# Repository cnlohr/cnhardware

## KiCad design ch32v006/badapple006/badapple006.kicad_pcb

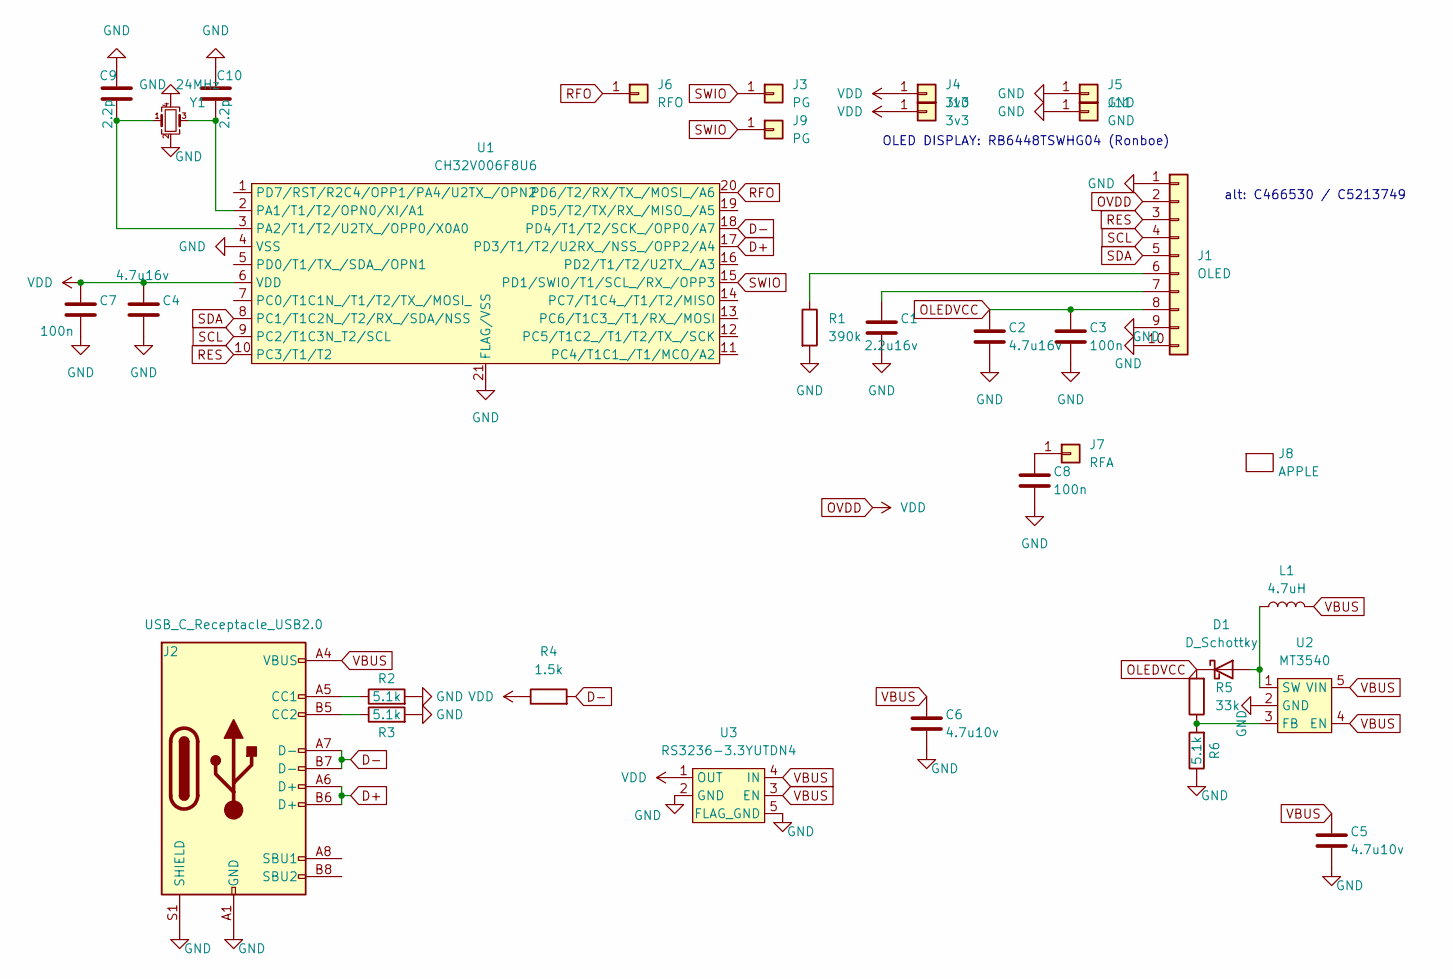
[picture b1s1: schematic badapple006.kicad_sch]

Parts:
C1: 2.2u16v; C_0402_1005Metric; LCSC C72203
C2: 4.7u16v; C_0603_1608Metric; LCSC C77045
C3, C7, C8: 100n; C_0402_1005Metric; LCSC C1525
C4: 4.7u16v; C_0402_1005Metric; LCSC C72203
C5, C6: 4.7u10v; C_0402_1005Metric; LCSC C23733
C9, C10: 2.2p; C_0402_1005Metric; LCSC C1559
D1: D_Schottky; D_SOD-323; LCSC C191023
J1: OLED; AFC42-S08FMA-1H; LCSC C466530
J2: USB_C_Receptacle_USB2.0; USB_C_Receptacle_HRO_TYPE-C-31-M-12; LCSC C2765186
J3, J9: PG; TestPoint_Pad_D1.0mm
J4, J10: 3v3; TestPoint_Pad_D1.0mm
J5, J11: GND; TestPoint_Pad_D1.0mm
J6: RFO; TestPoint_Pad_D1.0mm
J7: RFA; TestPoint_Pad_D1.0mm
J8: APPLE; apple
L1: 4.7uH; L_0603_1608Metric; LCSC C114862
R1: 390k; R_0402_1005Metric; LCSC C25782
R2, R3, R6: 5.1k; R_0402_1005Metric; LCSC C105872
R4: 1.5k; R_0402_1005Metric; LCSC C25867
R5: 33k; R_0402_1005Metric; LCSC C25779
U1: CH32V006F8U6; QFN-20-1EP_3x3mm_P0.4mm_EP1.65x1.65mm
U2: MT3540; SOT-23-5; LCSC C181744
U3: RS3236-3.3YUTDN4; xdfn-reg; LCSC C379350
Y1: 24MHz; Crystal_SMD_2016-4Pin_2.0x1.6mm; LCSC C2929397

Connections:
D+: J2.A6 (D+), J2.B6 (D+), U1.17 (PD3/T1/T2/U2RX_/NSS_/OPP2/A4)
D-: J2.A7 (D-), J2.B7 (D-), R4.2, U1.18 (PD4/T1/T2/SCK_/OPP0/A7)
GND: C1.2, C2.2, C3.2, C4.2, C5.2, C6.2, C7.2, C8.2, C9.1, C10.1, J1.1, J1.9, J1.10, J2.A1 (GND), J2.A12 (GND), J2.B1 (GND), J2.B12 (GND), J2.S1 (SHIELD), J5.1, J11.1, R1.2, R2.2, R3.2, R6.1, U1.4 (VSS), U1.21 (FLAG/VSS), U2.2 (GND), U3.2 (GND), U3.5 (FLAG_GND), Y1.2, Y1.4
unnamed: D1.2 (A), L1.1, U2.1 (SW)
unnamed: J1.6, R1.1
unnamed: C1.1, J1.7
unnamed: J2.A5 (CC1), R2.1
unnamed: J2.B5 (CC2), R3.1
unnamed: C8.1, J7.1
unnamed: C10.2, U1.2 (PA1/T1/T2/OPN0/XI/A1), Y1.3
unnamed: C9.2, U1.3 (PA2/T1/T2/U2TX_/OPP0/X0A0), Y1.1
unnamed: R5.1, R6.2, U2.3 (FB)
OLEDVCC: C2.1, C3.1, D1.1 (K), J1.8, R5.2
OVDD: C4.1, C7.1, J1.2, J4.1, J10.1, R4.1, U1.6 (VDD), U3.1 (OUT)
RES: J1.3, U1.10 (PC3/T1/T2)
RFO: J6.1, U1.20 (PD6/T2/RX/TX_/MOSI_/A6)
SCL: J1.4, U1.9 (PC2/T1C3N_T2/SCL)
SDA: J1.5, U1.8 (PC1/T1C2N_/T2/RX_/SDA/NSS)
SWIO: J3.1, J9.1, U1.15 (PD1/SWIO/T1/SCL_/RX_/OPP3)
VBUS: C5.1, C6.1, J2.A4 (VBUS), J2.A9 (VBUS), J2.B4 (VBUS), J2.B9 (VBUS), L1.2, U2.4 (EN), U2.5 (VIN), U3.3 (EN), U3.4 (IN)

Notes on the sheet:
alt: C466530 / C5213749
OLED DISPLAY: RB6448TSWHG04 (Ronboe)

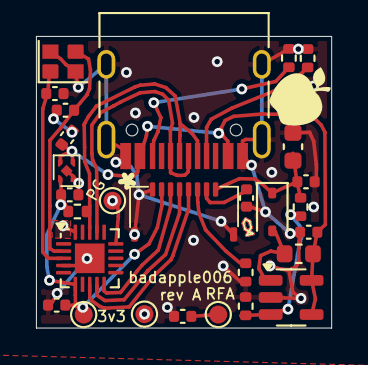
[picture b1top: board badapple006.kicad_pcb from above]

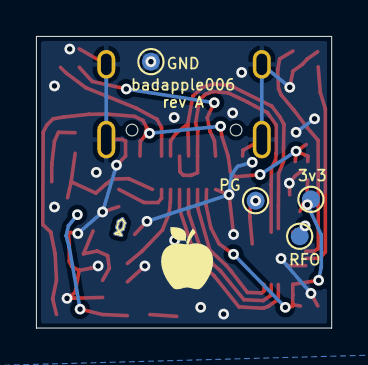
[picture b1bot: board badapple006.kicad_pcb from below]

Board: 2 copper layers, 16.4 x 16.2 mm, 34 parts (5 on the bottom side), 20 nets.

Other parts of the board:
J8#2: APPLE; apple

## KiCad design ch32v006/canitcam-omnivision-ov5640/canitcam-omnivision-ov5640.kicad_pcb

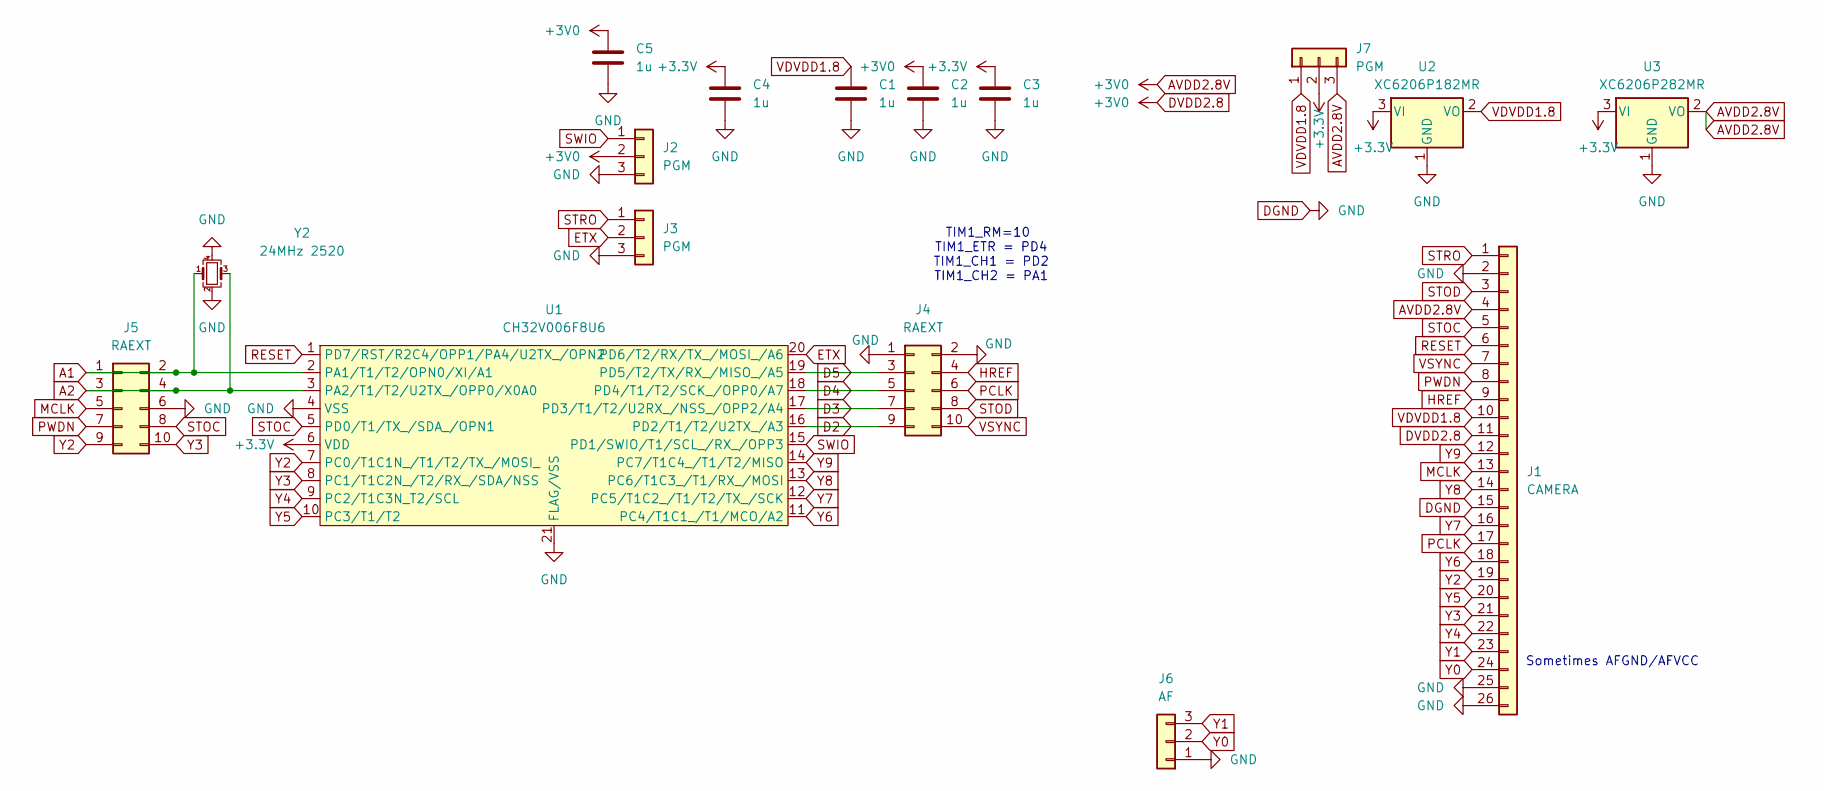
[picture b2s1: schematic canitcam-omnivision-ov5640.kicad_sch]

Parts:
C1, C2, C3, C4, C5: 1u; C_0402_1005Metric; LCSC C52923
J1: CAMERA; XUNPU_FPC-05F-24PH15; LCSC C2856831
J2, J3, J7: PGM; PinHeader_1x03_P2.54mm_Vertical; LCSC C2937625
J4, J5: RAEXT; PinHeader_2x05_P2.54mm_Vertical; LCSC C492422
J6: AF; PinHeader_1x03_P2.54mm_Vertical; LCSC C2937625
U1: CH32V006F8U6; QFN-20-1EP_3x3mm_P0.4mm_EP1.65x1.65mm; LCSC C42431288
U2: XC6206P182MR; SOT-23; LCSC C347373
U3: XC6206P282MR; SOT-23; LCSC C347374
Y2: 24MHz 2520; Crystal_SMD_2520-4Pin_2.5x2.0mm; LCSC C2965580

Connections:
+3.3V: C3.1, C4.1, J7.2, U1.6 (VDD), U2.3 (VI), U3.3 (VI)
A1: J5.1, J5.2, U1.2 (PA1/OSCI/A1/T1CH2/OPN0), Y2.1
A2: J5.3, J5.4, U1.3 (PA2/OSCO/A0/T1CH2N/OPP0/AETR2), Y2.3
AVDD2.8V: C2.1, C5.1, J1.4, J1.11, J2.2, J7.3, U3.2 (VO)
D2: J4.9, U1.16 (PD2/A3/T1CH1/T2CH3/T1CH2N)
D3: J4.7, U1.17 (PD3/A4/T2CH2/AETR/UCTS/T1CH4)
D4: J4.5, U1.18 (PD4/A7/UCK/T2CH1ETR/OPO/T1CH4ETR)
D5: J4.3, U1.19 (PD5/A5/UTX/T2CH4/URX)
DGND: C1.2, C2.2, C3.2, C4.2, C5.2, J1.2, J1.15, J1.25, J1.26, J2.3, J3.3, J4.1, J4.2, J5.6, J6.1, U1.4 (VSS), U1.21 (GND), U2.1 (GND), U3.1 (GND), Y2.2, Y2.4
ETX: J3.2, U1.20 (PD6/A7/URX/T2CH3/UTX)
HREF: J1.9, J4.4
MCLK: J1.13, J5.5
PCLK: J1.17, J4.6
PWDN: J1.8, J5.7
RESET: J1.6, U1.1 (PD7/NRST/T2CH4/OPP1/UCK)
STOC: J1.5, J5.8, U1.5 (PD0/T1CH1N/OPN1/SDA/UTX)
STOD: J1.3, J4.8
STRO: J1.1, J3.1
SWIO: J2.1, U1.15 (PD1/SWIO/AETR/T1CH3/SCL/URX)
VDVDD1.8: C1.1, J1.10, J7.1, U2.2 (VO)
VSYNC: J1.7, J4.10
Y0: J1.24, J6.2
Y1: J1.23, J6.3
Y2: J1.19, J5.9, U1.7 (PC0/T2CH3/UTX/NSS/T1CH3)
Y3: J1.21, J5.10, U1.8 (PC1/SDA/NSS/T2CH4/T2CH1ETR/T1BKIN/URX)
Y4: J1.22, U1.9 (PC2/SCL/URTS/T1BKIN/AETR/T2CH2/T1ETR)
Y5: J1.20, U1.10 (PC3/T1CH3/T1CHIN/UCTS)
Y6: J1.18, U1.11 (PC4/A2/T1CH4/MCO/T1CH1CH2N)
Y7: J1.16, U1.12 (PC5/SCK/T1ETR/T2CH1ETR/SCL/UCK/T1CH3)
Y8: J1.14, U1.13 (PC6/MOSI/T1CH1CH3/UCTS/SDA)
Y9: J1.12, U1.14 (PC7/MISO/T1CH2/T2CH2/URTS)

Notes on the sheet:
Sometimes AFGND/AFVCC
TIM1_RM=10 TIM1_ETR = PD4 TIM1_CH1 = PD2 TIM1_CH2 = PA1

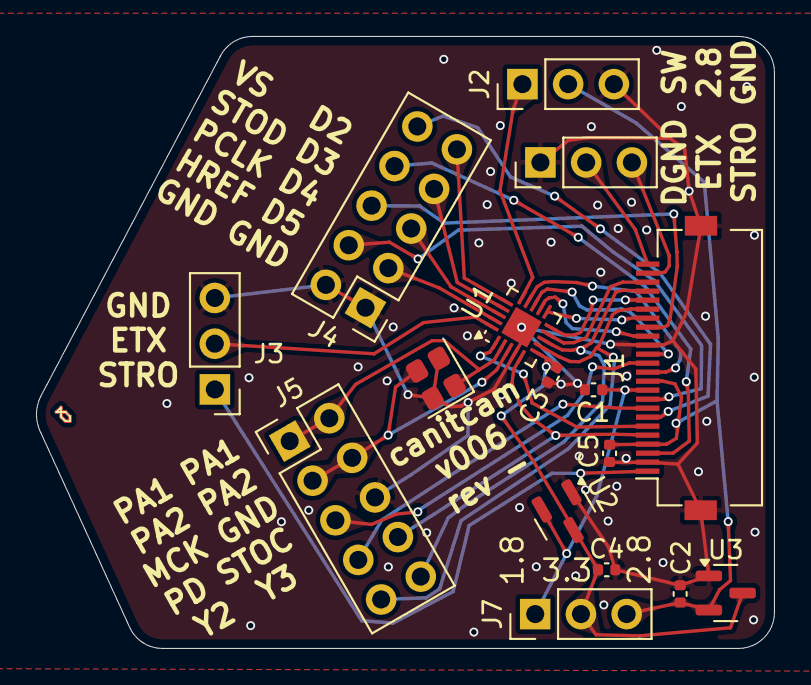
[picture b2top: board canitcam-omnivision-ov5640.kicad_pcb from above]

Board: 2 copper layers, 41.0 x 34.0 mm, 16 parts (0 on the bottom side), 31 nets.

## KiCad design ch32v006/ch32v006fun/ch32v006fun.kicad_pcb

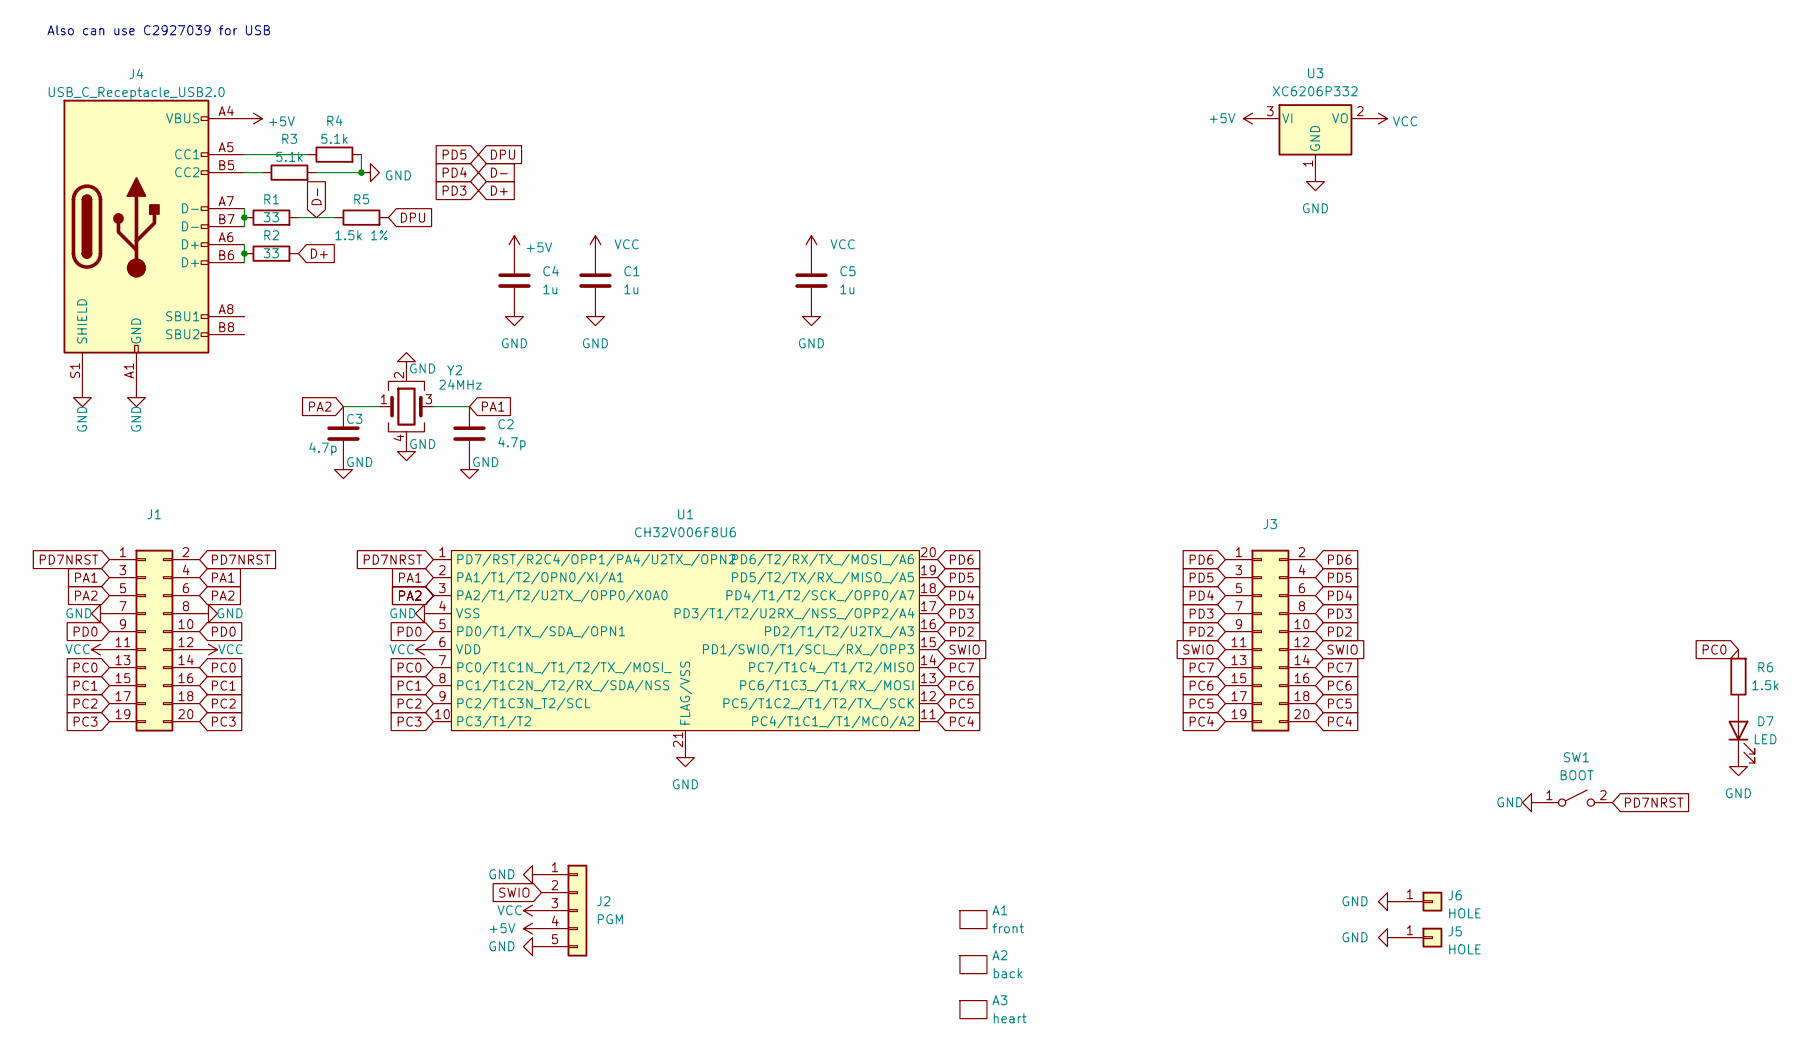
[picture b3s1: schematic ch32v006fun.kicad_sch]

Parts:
A1: front; OctoFront
A2: back; OctoBack
A3: heart; Heart
C1, C4, C5: 1u; C_0402_1005Metric; LCSC C52923
C2, C3: 4.7p; C_0402_1005Metric; LCSC C325453
D7: LED; LED_0402_1005Metric; LCSC C74342
J1, J3: PinHeader_2x10_P2.54mm_Vertical; LCSC C124359
J2: PGM; PinHeader_1x05_P2.54mm_Vertical; LCSC C358687
J4: USB_C_Receptacle_USB2.0; USB_C_Receptacle_HRO_TYPE-C-31-M-12; LCSC C709358
J5, J6: HOLE; MountingHole_2.2mm_M2_DIN965_Pad
R1, R2: 33; R_0402_1005Metric; LCSC C25105
R3, R4: 5.1k; R_0402_1005Metric; LCSC C25905
R5: 1.5k 1%; R_0402_1005Metric; LCSC C25867
R6: 1.5k; R_0402_1005Metric; LCSC C25867
SW1: BOOT; TS-1187A-B-A-B-TACTILE; LCSC C318884
U1: CH32V006F8U6; QFN-20-1EP_3x3mm_P0.4mm_EP1.65x1.65mm; JLCPCB C42431288
U3: XC6206P332; SOT-23; LCSC C5446
Y2: 24MHz; Crystal_SMD_2520-4Pin_2.5x2.0mm; LCSC C435195

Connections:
+5V: C4.1, J2.4, J4.A4 (VBUS), J4.A9 (VBUS), J4.B4 (VBUS), J4.B9 (VBUS), U3.3 (VI)
D+: J3.7, J3.8, R2.2, U1.17 (PD3/T1/T2/U2RX_/NSS_/OPP2/A4)
D-: J3.5, J3.6, R1.2, R5.1, U1.18 (PD4/T1/T2/SCK_/OPP0/A7)
DPU: J3.3, J3.4, R5.2, U1.19 (PD5/T2/TX/RX_/MISO_/A5)
GND: C1.2, C2.2, C3.2, C4.2, C5.2, D7.1 (K), J1.7, J1.8, J2.1, J2.5, J4.A1 (GND), J4.A12 (GND), J4.B1 (GND), J4.B12 (GND), J4.S1 (SHIELD), J5.1, J6.1, R3.2, R4.2, SW1.1 (A), U1.4 (VSS), U1.21 (FLAG/VSS), U3.1 (GND), Y2.2, Y2.4
unnamed: D7.2 (A), R6.1
unnamed: J4.A5 (CC1), R4.1
unnamed: J4.B5 (CC2), R3.1
unnamed: J4.A6 (D+), J4.B6 (D+), R2.1
unnamed: J4.A7 (D-), J4.B7 (D-), R1.1
PA1: C2.1, J1.3, J1.4, U1.2 (PA1/T1/T2/OPN0/XI/A1), Y2.3
PA2: C3.1, J1.5, J1.6, U1.3 (PA2/T1/T2/U2TX_/OPP0/X0A0), Y2.1
PC0: J1.13, J1.14, R6.2, U1.7 (PC0/T1C1N_/T1/T2/TX_/MOSI_)
PC1: J1.15, J1.16, U1.8 (PC1/T1C2N_/T2/RX_/SDA/NSS)
PC2: J1.17, J1.18, U1.9 (PC2/T1C3N_T2/SCL)
PC3: J1.19, J1.20, U1.10 (PC3/T1/T2)
PC4: J3.19, J3.20, U1.11 (PC4/T1C1_/T1/MCO/A2)
PC5: J3.17, J3.18, U1.12 (PC5/T1C2_/T1/T2/TX_/SCK)
PC6: J3.15, J3.16, U1.13 (PC6/T1C3_/T1/RX_/MOSI)
PC7: J3.13, J3.14, U1.14 (PC7/T1C4_/T1/T2/MISO)
PD0: J1.9, J1.10, U1.5 (PD0/T1/TX_/SDA_/OPN1)
PD2: J3.9, J3.10, U1.16 (PD2/T1/T2/U2TX_/A3)
PD6: J3.1, J3.2, U1.20 (PD6/T2/RX/TX_/MOSI_/A6)
PD7NRST: J1.1, J1.2, SW1.2 (B), U1.1 (PD7/RST/R2C4/OPP1/PA4/U2TX_/OPN2)
SWIO: J2.2, J3.11, J3.12, U1.15 (PD1/SWIO/T1/SCL_/RX_/OPP3)
VCC: C1.1, C5.1, J1.11, J1.12, J2.3, U1.6 (VDD), U3.2 (VO)

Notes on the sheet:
Also can use C2927039 for USB

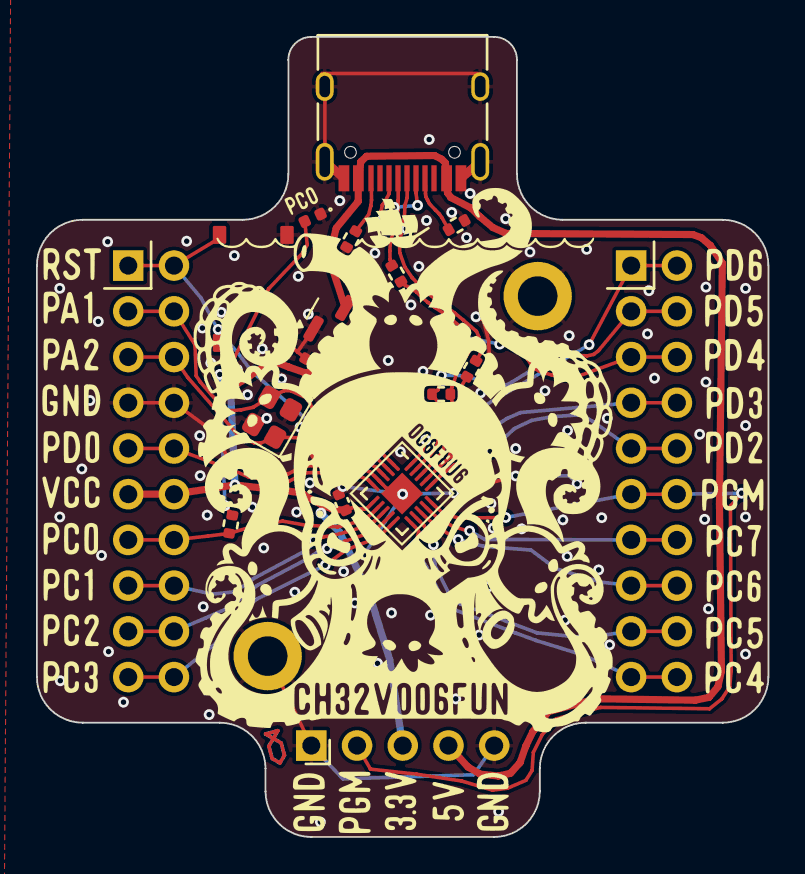
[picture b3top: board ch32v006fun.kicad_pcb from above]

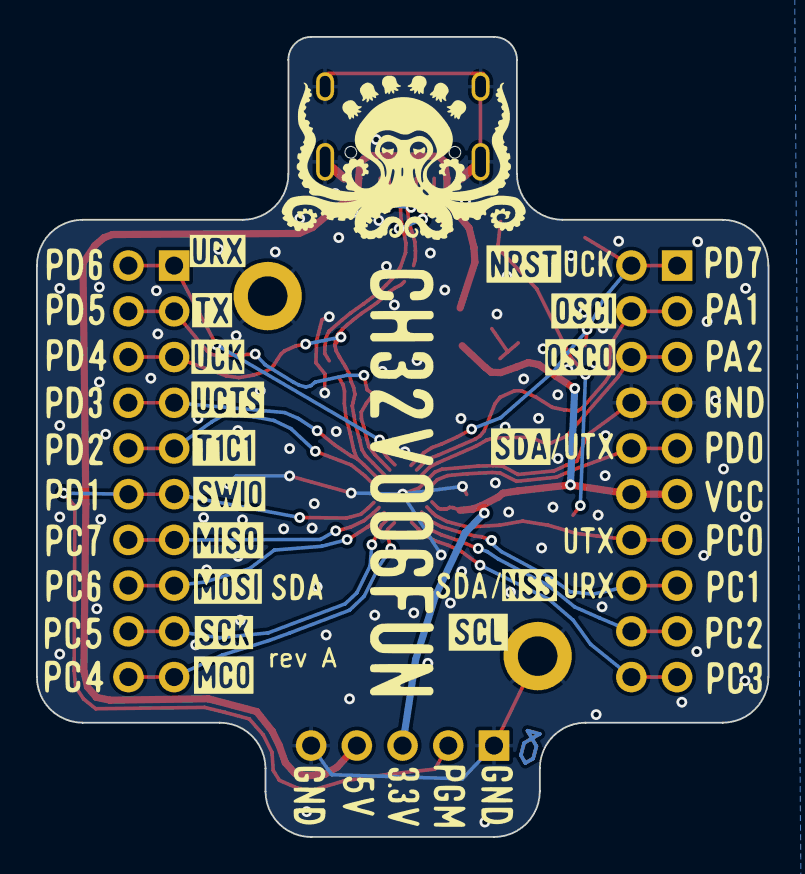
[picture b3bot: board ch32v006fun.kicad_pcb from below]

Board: 2 copper layers, 40.6 x 44.5 mm, 25 parts (2 on the bottom side), 26 nets.

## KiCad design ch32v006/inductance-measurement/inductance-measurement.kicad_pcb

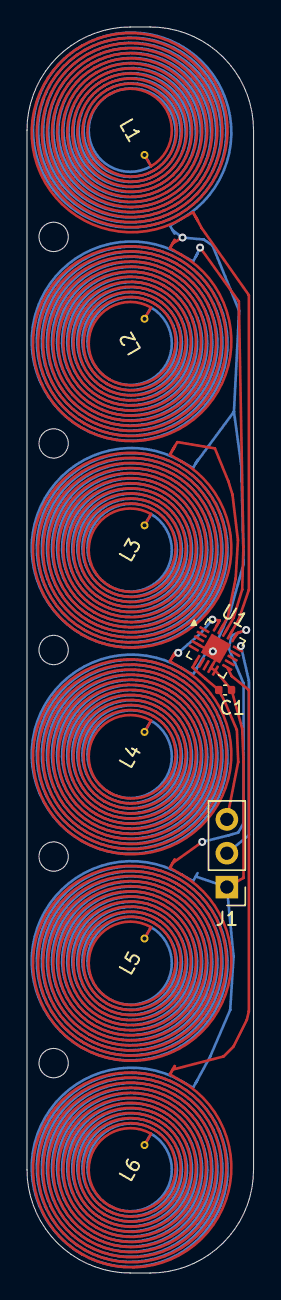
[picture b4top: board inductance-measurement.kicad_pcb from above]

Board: 2 copper layers, 17.0 x 93.5 mm, 14 parts (1 on the bottom side), 9 nets.

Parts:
C1: C; C_0402_1005Metric
H1, H2, H3, H4, H5: MH; MountingHole_2.2mm_M2
J1: PGM; PinHeader_1x03_P2.54mm_Vertical
L1, L2, L3, L4, L5, L6: L; 15mmCoil
U1: CH32V006F8U6; QFN-20-1EP_3x3mm_P0.4mm_EP1.65x1.65mm

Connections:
+3.3V: C1.1, J1.3, U1.6 (VDD)
GND: C1.2, J1.1, L1.2, L2.2, L3.2, L4.2, L5.2, L6.2, U1.4 (VSS), U1.9 (PC2/T1C3N_T2/SCL), U1.10 (PC3/T1/T2), U1.21 (FLAG/VSS)
unnamed: L6.1, U1.11 (PC4/T1C1_/T1/MCO/A2)
unnamed: L5.1, U1.16 (PD2/T1/T2/U2TX_/A3)
unnamed: L1.1, U1.17 (PD3/T1/T2/U2RX_/NSS_/OPP2/A4)
unnamed: L2.1, U1.18 (PD4/T1/T2/SCK_/OPP0/A7)
unnamed: L3.1, U1.19 (PD5/T2/TX/RX_/MISO_/A5)
unnamed: L4.1, U1.20 (PD6/T2/RX/TX_/MOSI_/A6)
SWIO: J1.2, U1.15 (PD1/SWIO/T1/SCL_/RX_/OPP3)

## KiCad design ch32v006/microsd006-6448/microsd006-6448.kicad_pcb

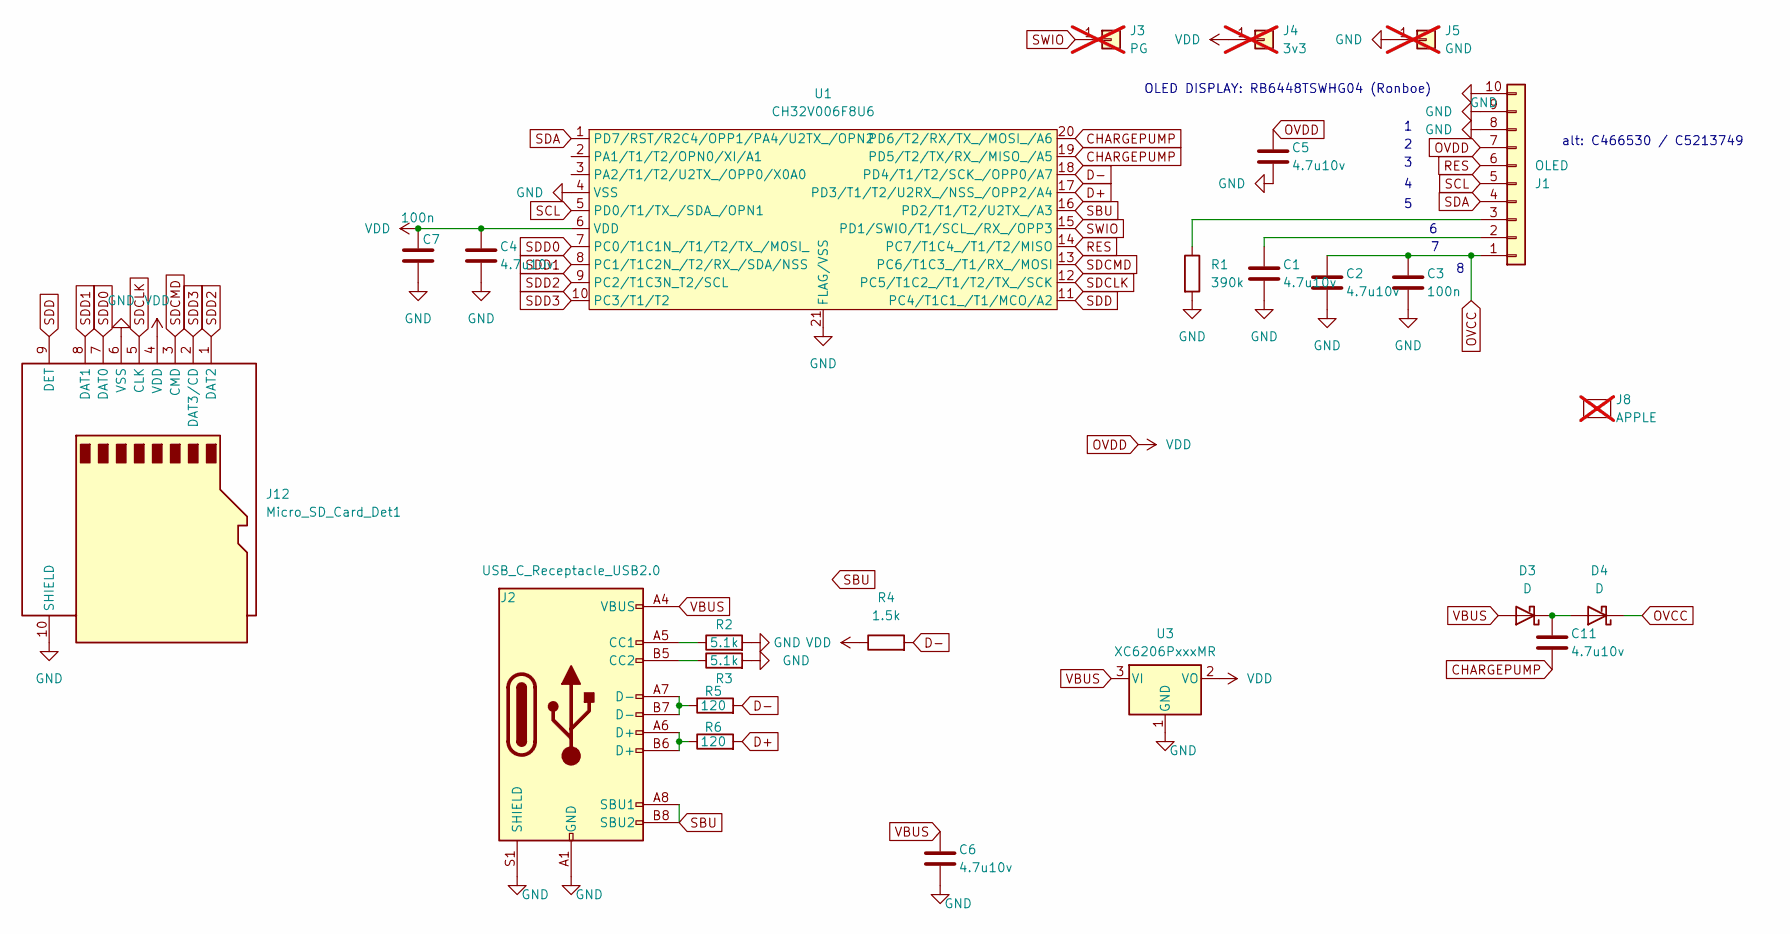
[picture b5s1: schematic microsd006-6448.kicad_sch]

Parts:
C1, C2, C4, C5, C6, C11: 4.7u10v; C_0402_1005Metric; LCSC C23733
C3, C7: 100n; C_0402_1005Metric; LCSC C1525
D3, D4: D; D_SOD-323; LCSC C191023
J1: OLED; AFC42-S08FMA-1H; LCSC C466530
J2: USB_C_Receptacle_USB2.0; USB_C_Receptacle_HRO_TYPE-C-31-M-12; LCSC C2765186
J3: PG; TestPoint_Pad_D1.0mm; not fitted
J4: 3v3; TestPoint_Pad_D1.0mm; not fitted
J5: GND; TestPoint_Pad_D1.0mm; not fitted
J8: APPLE; apple; not fitted
J12: Micro_SD_Card_Det1; MicroSD-C393941-SHOU-HAN-TF-PUSH-TINY; LCSC C22383473
R1: 390k; R_0402_1005Metric; LCSC C25782
R2, R3: 5.1k; R_0402_1005Metric; LCSC C105872
R4: 1.5k; R_0402_1005Metric; LCSC C25867
R5, R6: 120; R_0402_1005Metric; LCSC C25079
U1: CH32V006F8U6; QFN-20-1EP_3x3mm_P0.4mm_EP1.65x1.65mm; LCSC C42431288
U3: XC6206PxxxMR; SOT-23-3; LCSC C5446

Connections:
CHARGEPUMP: C11.2, U1.19 (PD5/T2/TX/RX_/MISO_/A5), U1.20 (PD6/T2/RX/TX_/MOSI_/A6)
D+: R6.2, U1.17 (PD3/T1/T2/U2RX_/NSS_/OPP2/A4)
D-: R4.2, R5.2, U1.18 (PD4/T1/T2/SCK_/OPP0/A7)
GND: C1.2, C2.2, C3.2, C4.2, C5.2, C6.2, C7.2, J1.8, J1.9, J1.10, J2.A1 (GND), J2.A12 (GND), J2.B1 (GND), J2.B12 (GND), J2.S1 (SHIELD), J5.1, J12.6 (VSS), J12.10 (SHIELD), R1.2, R2.2, R3.2, U1.4 (VSS), U1.21 (FLAG/VSS), U3.1 (GND)
unnamed: C11.1, D3.1 (K), D4.2 (A)
unnamed: C1.1, J1.2
unnamed: J1.3, R1.1
unnamed: J2.A5 (CC1), R2.1
unnamed: J2.B5 (CC2), R3.1
unnamed: J2.A6 (D+), J2.B6 (D+), R6.1
unnamed: J2.A7 (D-), J2.B7 (D-), R5.1
OVCC: C2.1, C3.1, D4.1 (K), J1.1
OVDD: C4.1, C5.1, C7.1, J1.7, J4.1, J12.4 (VDD), R4.1, U1.6 (VDD), U3.2 (VO)
RES: J1.6, U1.14 (PC7/T1C4_/T1/T2/MISO)
SBU: J2.A8 (SBU1), J2.B8 (SBU2), U1.16 (PD2/T1/T2/U2TX_/A3)
SCL: J1.5, U1.5 (PD0/T1/TX_/SDA_/OPN1)
SDA: J1.4, U1.1 (PD7/RST/R2C4/OPP1/PA4/U2TX_/OPN2)
SDCLK: J12.5 (CLK), U1.12 (PC5/T1C2_/T1/T2/TX_/SCK)
SDCMD: J12.3 (CMD), U1.13 (PC6/T1C3_/T1/RX_/MOSI)
SDD: J12.9 (DET), U1.11 (PC4/T1C1_/T1/MCO/A2)
SDD0: J12.7 (DAT0), U1.7 (PC0/T1C1N_/T1/T2/TX_/MOSI_)
SDD1: J12.8 (DAT1), U1.8 (PC1/T1C2N_/T2/RX_/SDA/NSS)
SDD2: J12.1 (DAT2), U1.9 (PC2/T1C3N_T2/SCL)
SDD3: J12.2 (DAT3/CD), U1.10 (PC3/T1/T2)
SWIO: J3.1, U1.15 (PD1/SWIO/T1/SCL_/RX_/OPP3)
VBUS: C6.1, D3.2 (A), J2.A4 (VBUS), J2.A9 (VBUS), J2.B4 (VBUS), J2.B9 (VBUS), U3.3 (VI)

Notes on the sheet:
alt: C466530 / C5213749
OLED DISPLAY: RB6448TSWHG04 (Ronboe)

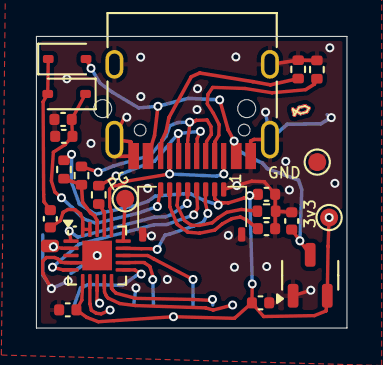
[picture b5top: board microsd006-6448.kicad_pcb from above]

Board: 2 copper layers, 17.2 x 16.2 mm, 24 parts (1 on the bottom side), 26 nets.

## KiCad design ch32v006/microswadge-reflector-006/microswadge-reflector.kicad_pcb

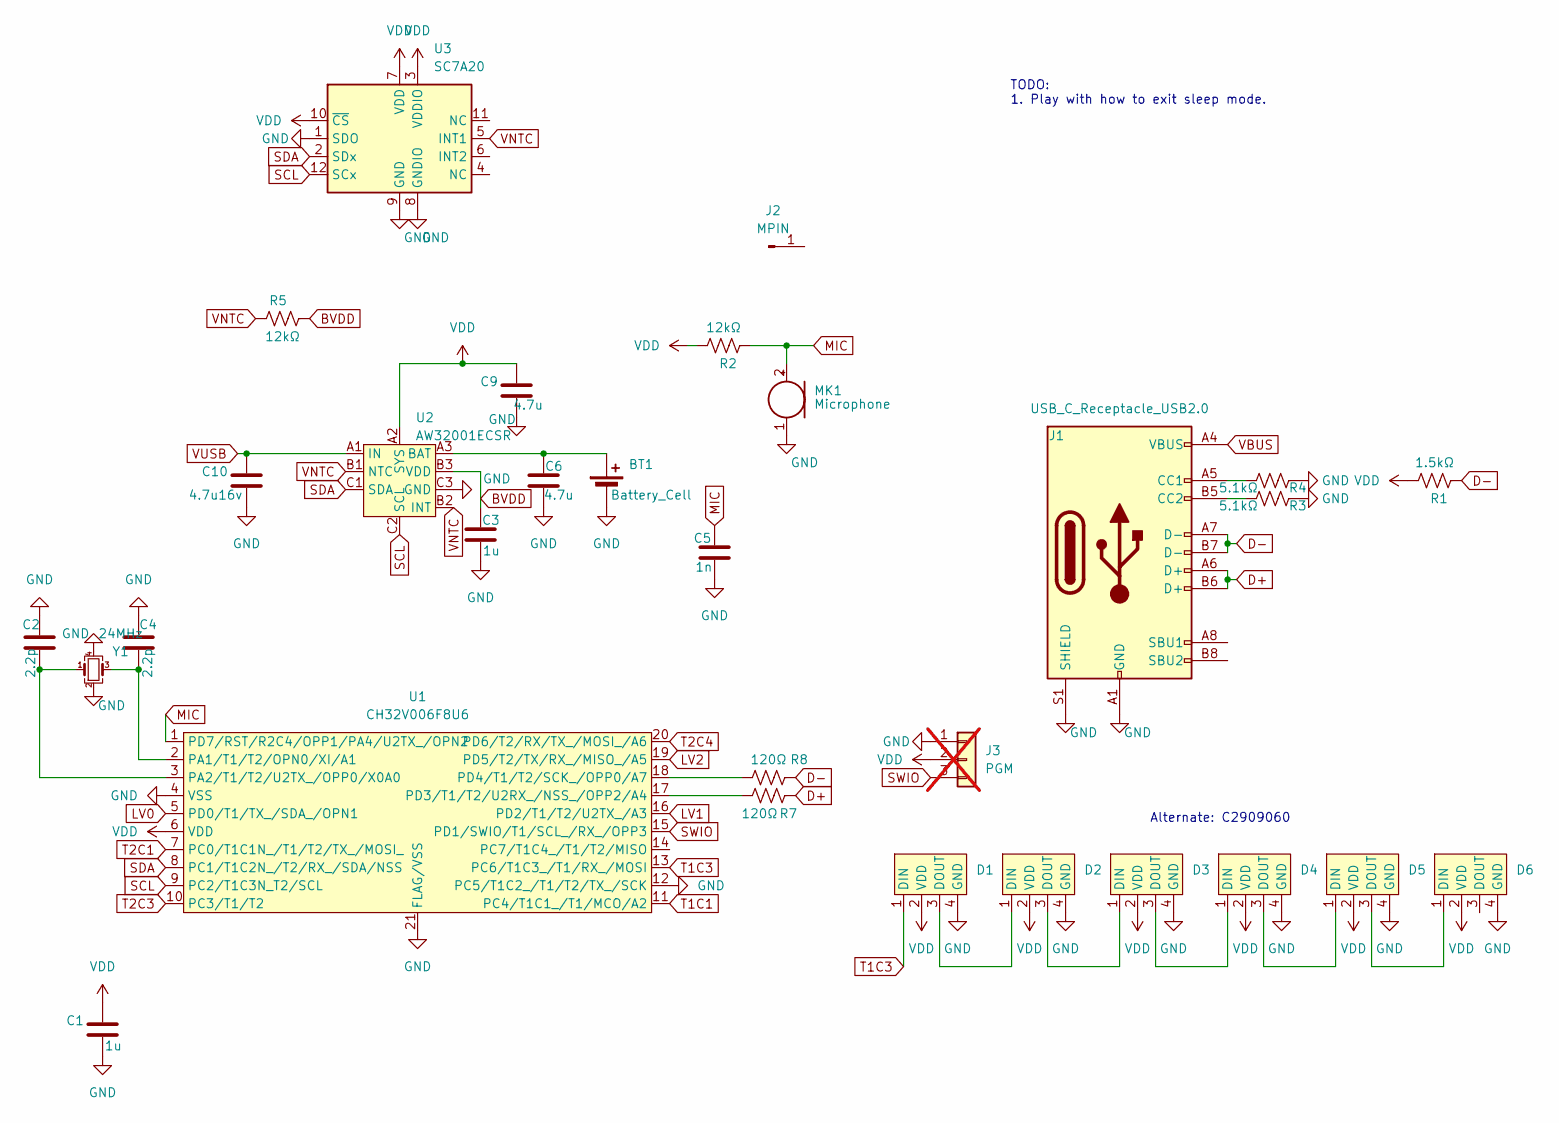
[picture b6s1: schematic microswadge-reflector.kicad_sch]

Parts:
BT1: Battery_Cell; CR2450-TWOPAD; LCSC C964809
C1, C3: 1u; C_0402_1005Metric; LCSC C14445
C2, C4: 2.2p; C_0402_1005Metric; LCSC C1559
C5: 1n; C_0402_1005Metric; LCSC C1523
C6, C9: 4.7u; C_0402_1005Metric; LCSC C23733
C10: 4.7u16v; C_0603_1608Metric; LCSC C19666
D1, D2, D3, D4, D5, D6: LC8812-SIDE-4020; LCSC C5378721
J1: USB_C_Receptacle_USB2.0; USB_C_Receptacle_HRO_TYPE-C-31-M-12; LCSC C2765186
J2: MPIN; TestPoint_Pad_D4.0mm
J3: PGM; PinHeader_1x03_P2.54mm_Vertical; not fitted
MK1: Microphone; INGHAi_MIC_GMI4013S-2C58DB; LCSC C529870
R1: 1.5kΩ; R_0402_1005Metric; LCSC C25867
R2, R5: 12kΩ; R_0402_1005Metric; LCSC C25752
R3, R4: 5.1kΩ; R_0402_1005Metric; LCSC C25905
R7, R8: 120Ω; R_0402_1005Metric; LCSC C25079
U1: CH32V006F8U6; QFN-20-1EP_3x3mm_P0.4mm_EP1.65x1.65mm
U2: AW32001ECSR; WLCSP-9-P0.5mm; LCSC C5125890
U3: SC7A20; LGA-12_2x2mm_P0.5mm; LCSC C5126709
Y1: 24MHz; Crystal_SMD_2016-4Pin_2.0x1.6mm; LCSC C2929397

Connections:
BVDD: C3.1, R5.1, U2.B3 (VDD)
D+: J1.A6 (D+), J1.B6 (D+), R7.2
D-: J1.A7 (D-), J1.B7 (D-), R1.2, R8.2
GND: BT1.2 (-), C1.2, C2.1, C3.2, C4.1, C5.2, C6.2, C9.2, C10.2, D1.4 (GND), D2.4 (GND), D3.4 (GND), D4.4 (GND), D5.4 (GND), D6.4 (GND), J1.A1 (GND), J1.A12 (GND), J1.B1 (GND), J1.B12 (GND), J1.S1 (SHIELD), J3.1, MK1.1 (-), R3.2, R4.2, U1.4 (VSS), U1.12 (PC5/T1C2_/T1/T2/TX_/SCK), U1.21 (FLAG/VSS), U2.C3 (GND), U3.1 (SDO), U3.8 (GNDIO), U3.9 (GND), Y1.2, Y1.4
LV0: U1.5 (PD0/T1/TX_/SDA_/OPN1)
LV1: U1.16 (PD2/T1/T2/U2TX_/A3)
LV2: U1.19 (PD5/T2/TX/RX_/MISO_/A5)
MIC: C5.1, MK1.2 (+), R2.2, U1.1 (PD7/RST/R2C4/OPP1/PA4/U2TX_/OPN2)
unnamed: BT1.1 (+), C6.1, U2.A3 (BAT)
unnamed: D1.3 (DOUT), D2.1 (DIN)
unnamed: D2.3 (DOUT), D3.1 (DIN)
unnamed: D3.3 (DOUT), D4.1 (DIN)
unnamed: D4.3 (DOUT), D5.1 (DIN)
unnamed: D5.3 (DOUT), D6.1 (DIN)
unnamed: J1.A5 (CC1), R4.1
unnamed: J1.B5 (CC2), R3.1
unnamed: C4.2, U1.2 (PA1/T1/T2/OPN0/XI/A1), Y1.3
unnamed: C2.2, U1.3 (PA2/T1/T2/U2TX_/OPP0/X0A0), Y1.1
unnamed: R7.1, U1.17 (PD3/T1/T2/U2RX_/NSS_/OPP2/A4)
unnamed: R8.1, U1.18 (PD4/T1/T2/SCK_/OPP0/A7)
SCL: U1.9 (PC2/T1C3N_T2/SCL), U2.C2 (SCL), U3.12 (SCx)
SDA: U1.8 (PC1/T1C2N_/T2/RX_/SDA/NSS), U2.C1 (SDA), U3.2 (SDx)
SWIO: J3.3, U1.15 (PD1/SWIO/T1/SCL_/RX_/OPP3)
T1C1: U1.11 (PC4/T1C1_/T1/MCO/A2)
T1C3: D1.1 (DIN), U1.13 (PC6/T1C3_/T1/RX_/MOSI)
T2C1: U1.7 (PC0/T1C1N_/T1/T2/TX_/MOSI_)
T2C3: U1.10 (PC3/T1/T2)
T2C4: U1.20 (PD6/T2/RX/TX_/MOSI_/A6)
VBUS: J1.A4 (VBUS), J1.A9 (VBUS), J1.B4 (VBUS), J1.B9 (VBUS)
VDD: C1.1, C9.1, D1.2 (VDD), D2.2 (VDD), D3.2 (VDD), D4.2 (VDD), D5.2 (VDD), D6.2 (VDD), J3.2, R1.1, R2.1, U1.6 (VDD), U2.A2 (SYS), U3.3 (VDDIO), U3.7 (VDD), U3.10 (~CS)
VNTC: R5.2, U2.B1 (NTC), U2.B2 (INT), U3.5 (INT1)
VUSB: C10.1, U2.A1 (IN)

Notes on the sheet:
Alternate: C2909060
TODO: 1. Play with how to exit sleep mode.

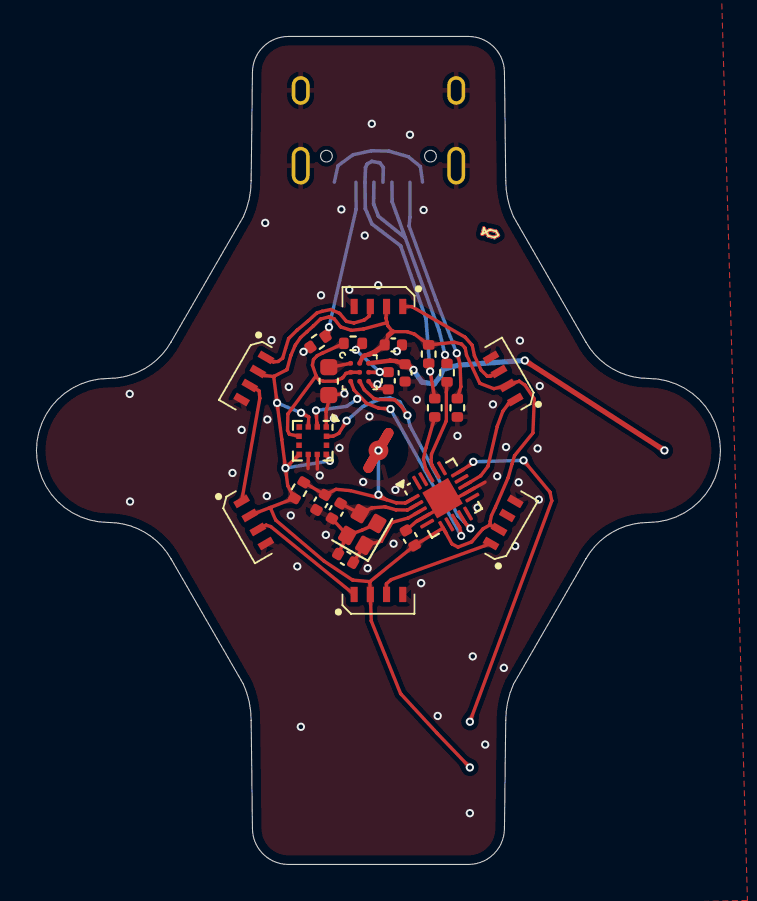
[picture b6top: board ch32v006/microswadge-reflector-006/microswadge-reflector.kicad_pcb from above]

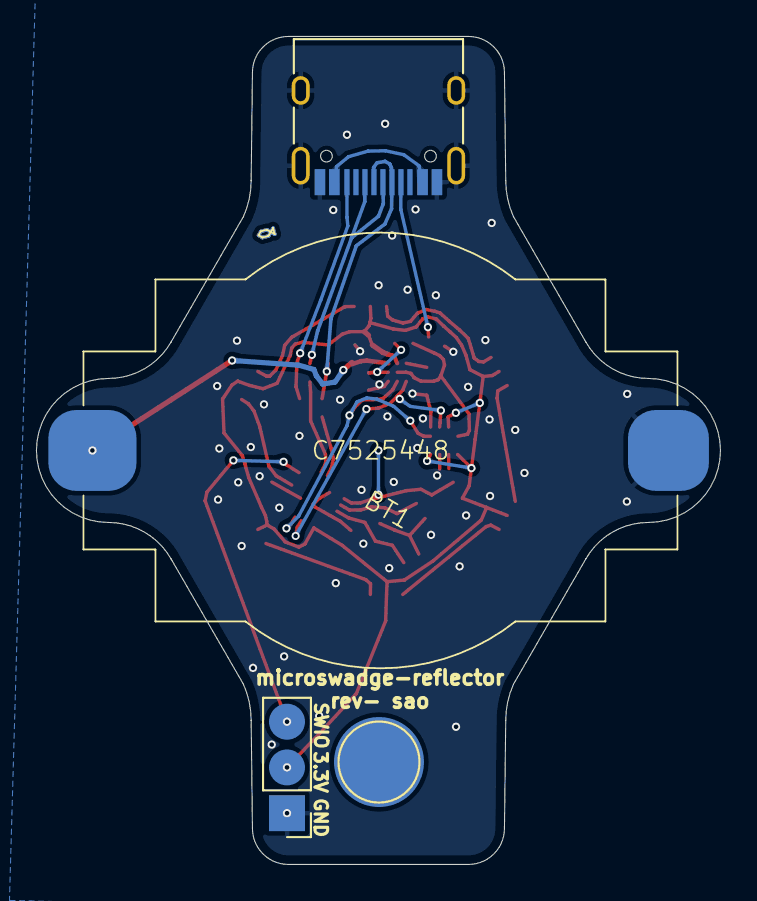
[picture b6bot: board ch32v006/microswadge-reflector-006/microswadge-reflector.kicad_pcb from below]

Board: 2 copper layers, 38.0 x 46.0 mm, 30 parts (4 on the bottom side), 25 nets.

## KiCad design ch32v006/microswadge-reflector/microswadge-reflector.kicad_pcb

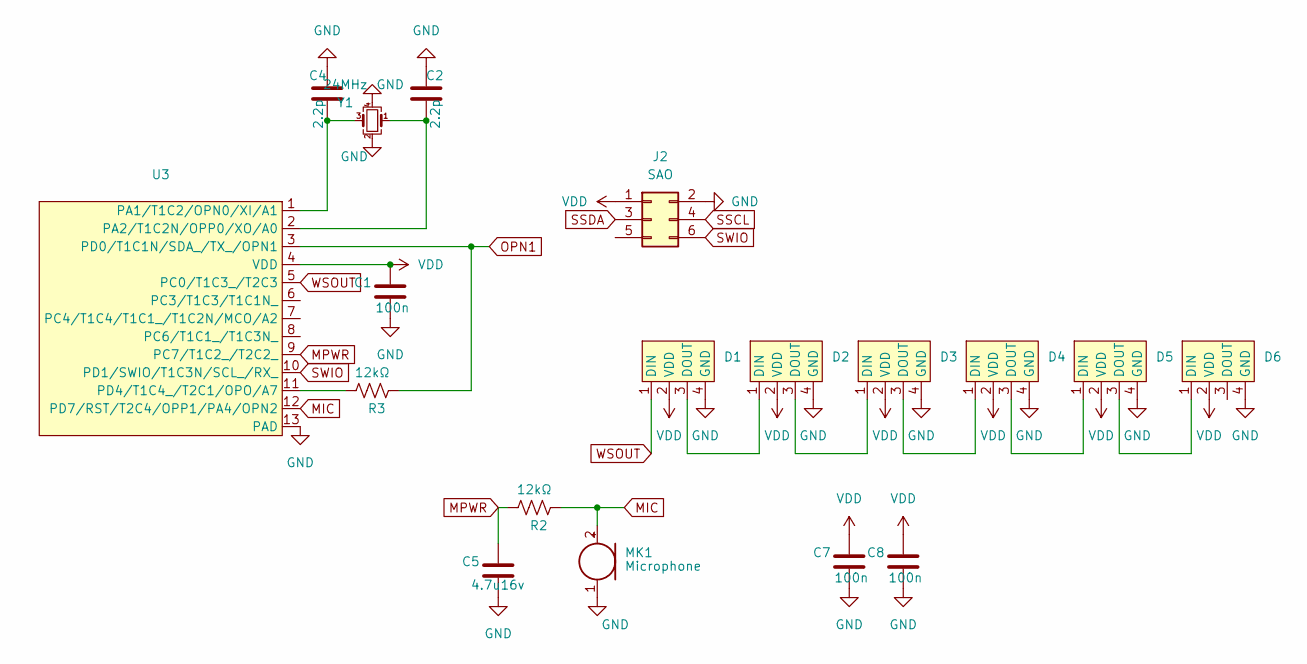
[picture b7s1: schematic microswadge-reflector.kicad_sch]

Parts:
C1, C7, C8: 100n; C_0402_1005Metric; LCSC C1525
C2, C4: 2.2p; C_0402_1005Metric; LCSC C1559
C5: 4.7u16v; C_0402_1005Metric; LCSC C72203
D1, D2, D3, D4, D5, D6: LC8812-SIDE-4020
J2: SAO; PinHeader_2x03_P2.54mm_Vertical_SMD
MK1: Microphone; INGHAi_MIC_GMI4013S-2C58DB; LCSC C529870
R2, R3: 12kΩ; R_0402_1005Metric; LCSC C22790
U3: QFN-12-P0.4-WCH
Y1: 24MHz; Crystal_SMD_2016-4Pin_2.0x1.6mm; LCSC C2929397

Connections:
GND: C1.2, C2.1, C4.1, C5.2, C7.2, C8.2, D1.4 (GND), D2.4 (GND), D3.4 (GND), D4.4 (GND), D5.4 (GND), D6.4 (GND), J2.2, MK1.1 (-), U3.13 (PAD), Y1.2, Y1.4
MIC: MK1.2 (+), R2.2, U3.12 (PD7/RST/T2C4/OPP1/PA4/OPN2)
MPWR: C5.1, R2.1, U3.9 (PC7/T1C2_/T2C2_)
unnamed: D1.3 (DOUT), D2.1 (DIN)
unnamed: D2.3 (DOUT), D3.1 (DIN)
unnamed: D3.3 (DOUT), D4.1 (DIN)
unnamed: D4.3 (DOUT), D5.1 (DIN)
unnamed: D5.3 (DOUT), D6.1 (DIN)
unnamed: C4.2, U3.1 (PA1/T1C2/OPN0/XI/A1), Y1.3
unnamed: C2.2, U3.2 (PA2/T1C2N/OPP0/XO/A0), Y1.1
unnamed: R3.1, U3.11 (PD4/T1C4_/T2C1/OPO/A7)
OPN1: R3.2, U3.3 (PD0/T1C1N/SDA_/TX_/OPN1)
SSCL: J2.4
SSDA: J2.3
SWIO: J2.6, U3.10 (PD1/SWIO/T1C3N/SCL_/RX_)
VDD: C1.1, C7.1, C8.1, D1.2 (VDD), D2.2 (VDD), D3.2 (VDD), D4.2 (VDD), D5.2 (VDD), D6.2 (VDD), J2.1, U3.4 (VDD)
WSOUT: D1.1 (DIN), U3.5 (PC0/T1C3_/T2C3)

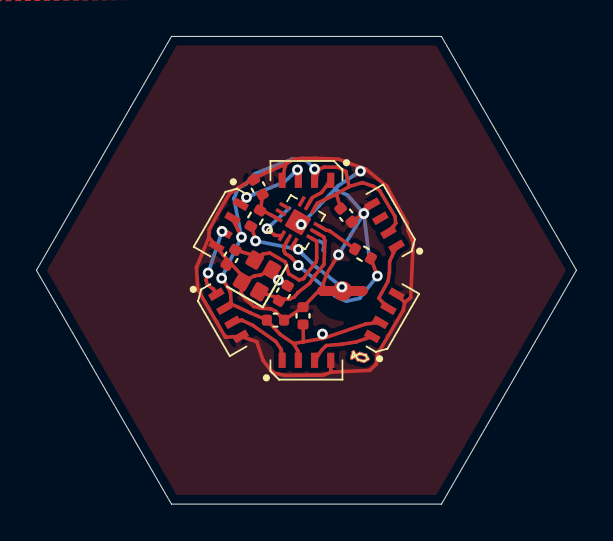
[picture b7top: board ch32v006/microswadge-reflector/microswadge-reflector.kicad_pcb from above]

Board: 2 copper layers, 30.0 x 26.0 mm, 18 parts (1 on the bottom side), 15 nets.
